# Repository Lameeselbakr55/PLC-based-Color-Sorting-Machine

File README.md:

# PLC-based-Color-Sorting-Machine
 This application is a prototype of machine building based on computer vision , PLC and scada system 

 ## Project Description 
 PLC based color sorting machine in which camera is added in the middle of the conveyor to detect color  according to image processing algorithm that decide if the product will pass or will be rejected. if the product is red, it    will pass and the conveyor operates again but if the product is green , the piston will operate and reject the product The whole process will be monitored on LabVIEW GUI and on Siemens Wincc Scada. Also there is a connection to SQL server database in which number of red and green products stored . Finally You can control and monitor the system operation remotely through server. 

## the machine consists of :
 * Conveyor with DC Motor to transport colored products 
 * Camera
 * Piston and Valve 
 * IR Sensor circuit 
 * Fatek PLC

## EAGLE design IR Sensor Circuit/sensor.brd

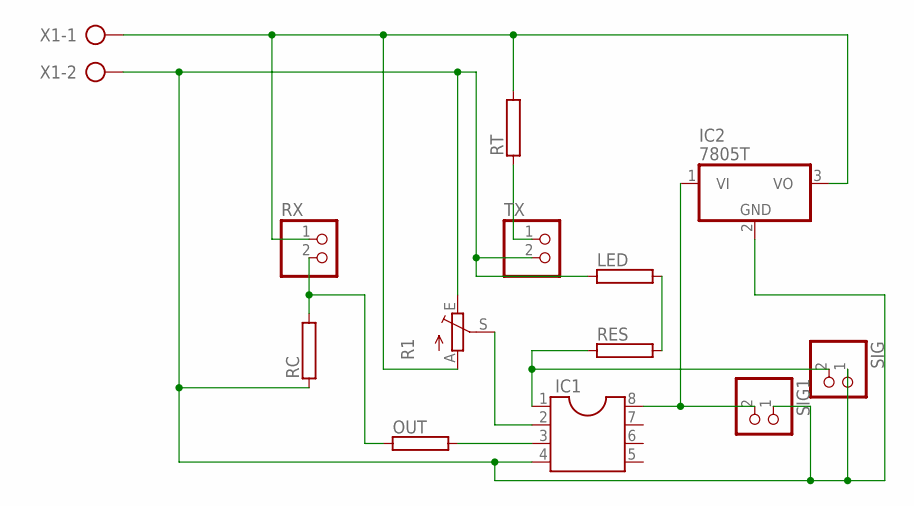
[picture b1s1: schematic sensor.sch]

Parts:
IC1: DIL8; DIL08
IC2: 7805T; TO220H
LED: RKH208-8R; KH208R-8
OUT: RKH208-8R; KH208R-8
R1: TRIM_EU-CA6V; CA6V
RC: RKH208-8R; KH208R-8
RES: RKH208-8R; KH208R-8
RT: RKH208-8R; KH208R-8
RX: PINHD-1X2; 1X02
SIG, SIG1: PINHD-1X2; 1X02
TX: PINHD-1X2; 1X02
X1: AK500/2-H

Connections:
unnamed: RT.1, TX.1
unnamed: IC2.3 (VO), R1.A, RT.2, RX.1, X1.1
unnamed: IC1.4, IC2.2 (GND), LED.1, R1.E, RC.1, SIG.1, SIG1.1, TX.2, X1.2
unnamed: OUT.1, RC.2, RX.2
unnamed: IC1.8, IC2.1 (VI), SIG1.2
unnamed: IC1.3, OUT.2
unnamed: IC1.2, R1.S
unnamed: IC1.1, RES.1, SIG.2
unnamed: LED.2, RES.2

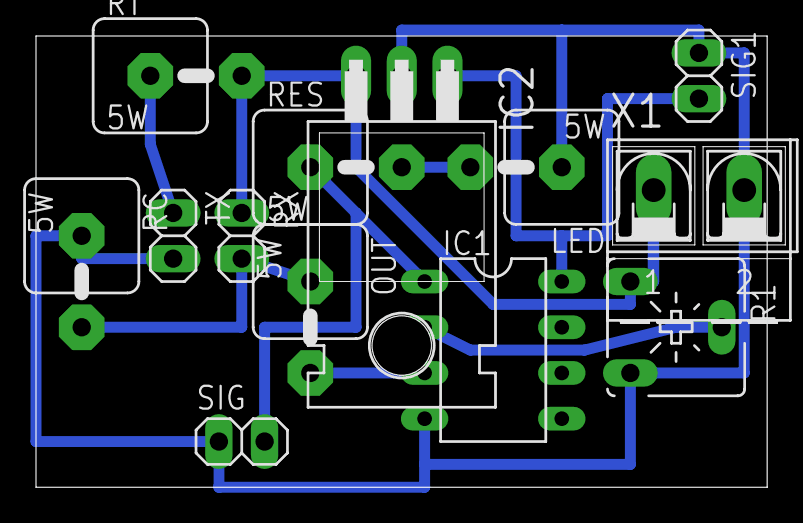
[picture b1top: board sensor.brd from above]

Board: 2 copper layers, 40.6 x 25.1 mm, 13 parts (0 on the bottom side), 9 nets.

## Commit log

2022-03-01 Eagle PCB of IR Sensor Circuit
2022-03-01 LabVIEW Project
2022-03-01 PLC Code
